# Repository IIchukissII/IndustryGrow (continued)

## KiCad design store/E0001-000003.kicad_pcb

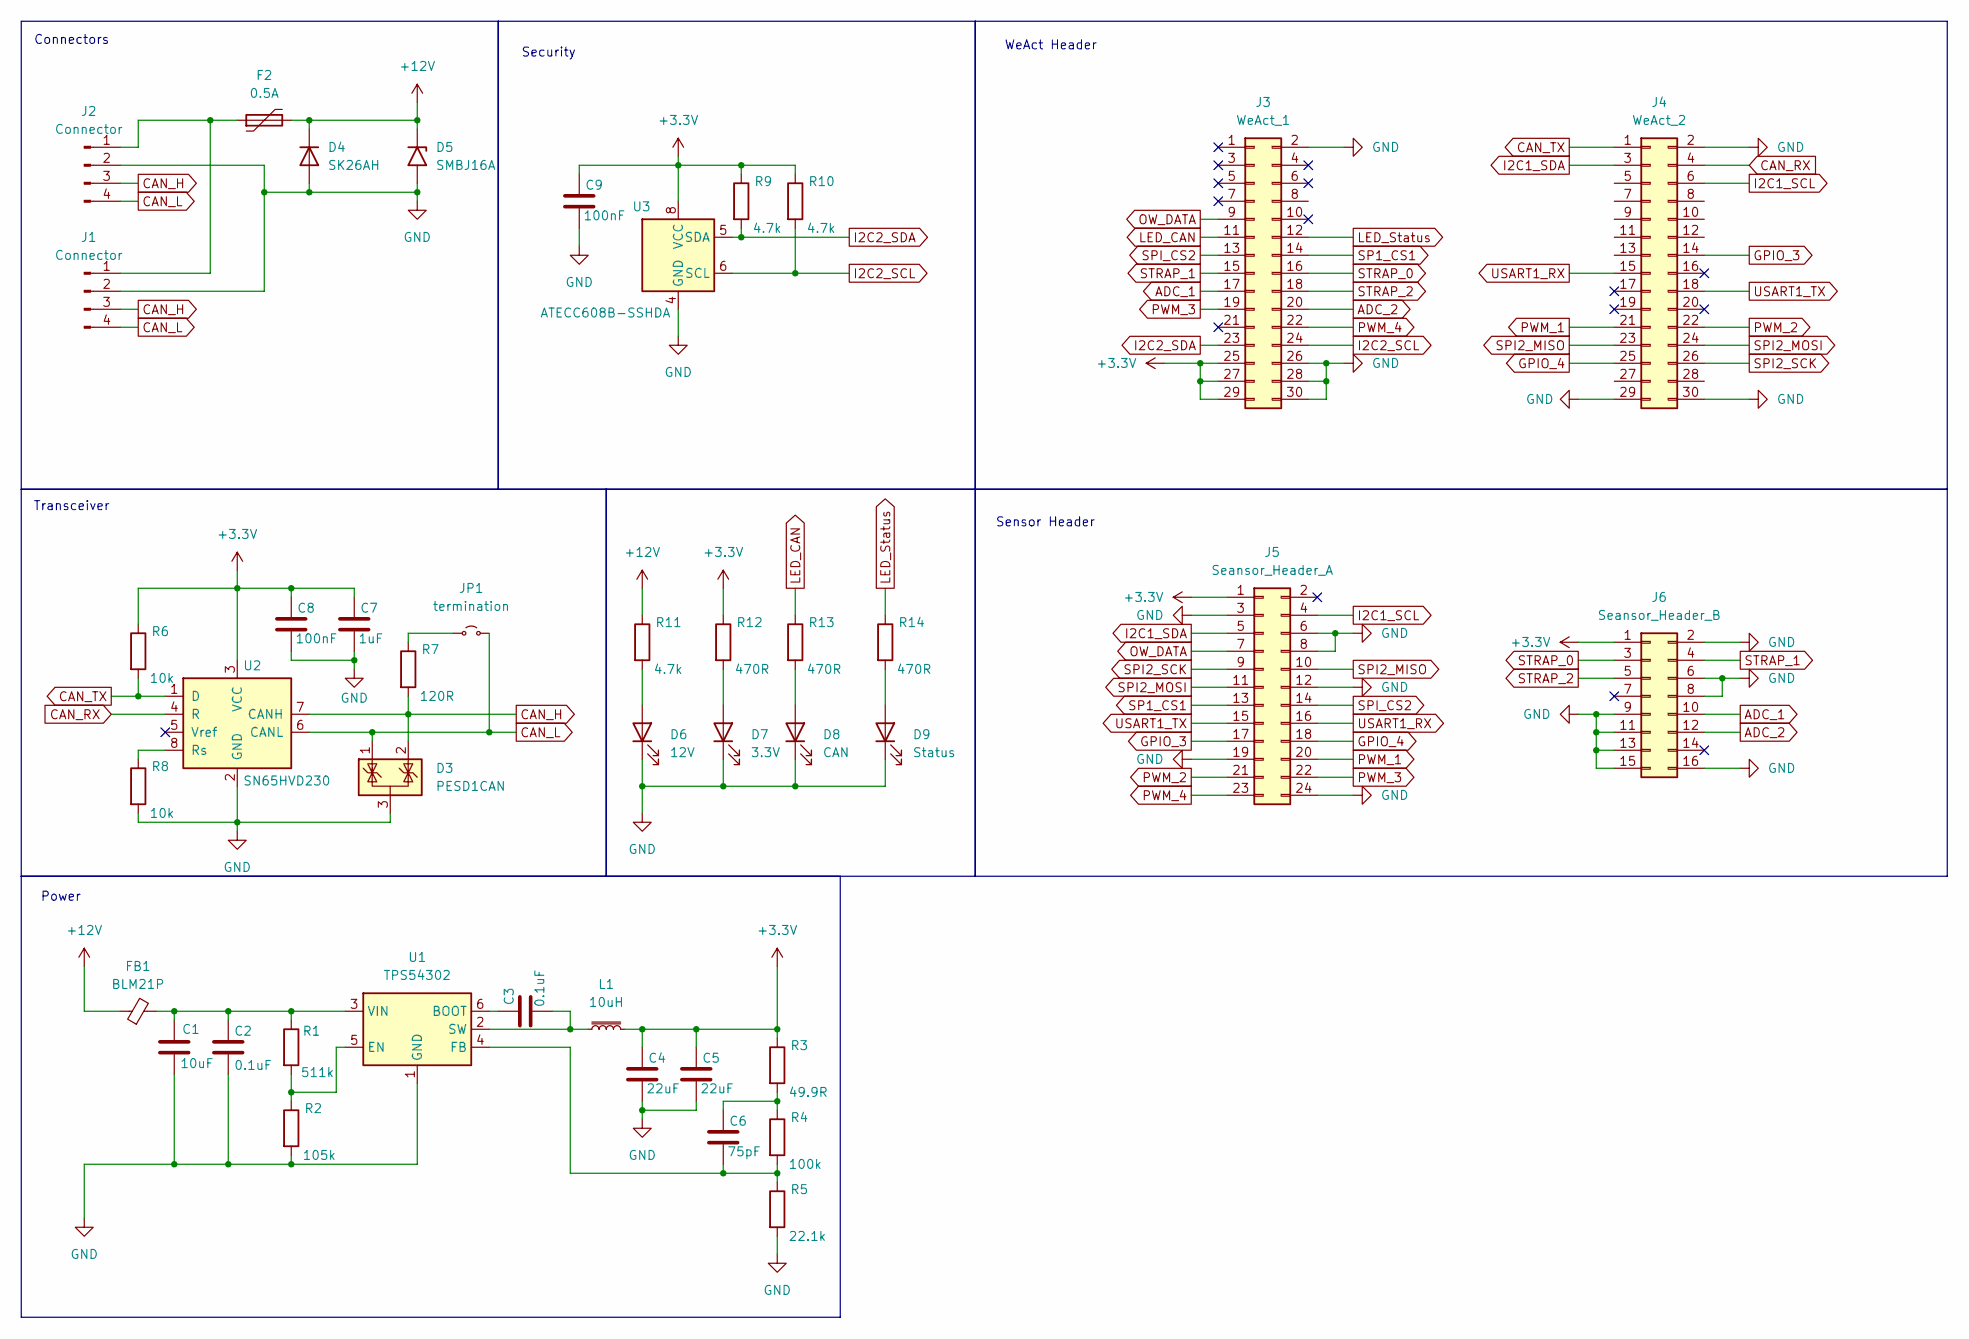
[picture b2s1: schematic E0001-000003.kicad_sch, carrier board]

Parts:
C1: 10uF; C_0805_2012Metric
C2, C3: 0.1uF; C_0805_2012Metric
C4, C5: 22uF; C_0805_2012Metric
C6: 75pF; C_0805_2012Metric
C7: 1uF; C_0805_2012Metric
C8, C9: 100nF; C_0805_2012Metric
D3: PESD1CAN; SOT-23
D4: SK26AH; D_SMA
D5: SMBJ16A; D_SMB
D6: 12V; LED_0805_2012Metric
D7: 3.3V; LED_0805_2012Metric
D8: CAN; LED_0805_2012Metric
D9: Status; LED_0805_2012Metric
F2: 0.5A; Fuse_0805_2012Metric
FB1: BLM21P; Fuse_0805_2012Metric
J1, J2: Connector; Molex_Micro-Fit_3.0_43045-0400_2x02_P3.00mm_Horizontal
J3: WeAct_1; PinSocket_2x15_P2.54mm_Vertical_SMD
J4: WeAct_2; PinSocket_2x15_P2.54mm_Vertical_SMD
J5: Seansor_Header_A; PinSocket_2x12_P2.54mm_Vertical_SMD
J6: Seansor_Header_B; PinSocket_2x08_P2.54mm_Vertical_SMD
JP1: termination; SolderJumper-2_P1.3mm_Open_Pad1.0x1.5mm
L1: 10uH; L_Sunlord_SWPA6045S
R1: 511k; R_0805_2012Metric
R2: 105k; R_0805_2012Metric
R3: 49.9R; R_0805_2012Metric
R4: 100k; R_0805_2012Metric
R5: 22.1k; R_0805_2012Metric
R6, R8: 10k; R_0805_2012Metric
R7: 120R; R_0805_2012Metric
R9, R10, R11: 4.7k; R_0805_2012Metric
R12, R13, R14: 470R; R_0805_2012Metric
U1: TPS54302; SOT-23-6
U2: SN65HVD230; SOIC-8_3.9x4.9mm_P1.27mm
U3: ATECC608B-SSHDA; SOIC-8_3.9x4.9mm_P1.27mm

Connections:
+3.3V: C4.1, C5.1, C7.1, C8.1, C9.1, J3.25, J3.27, J3.29, J5.1, J6.1, L1.2, R3.1, R6.1, R9.1, R10.1, R12.1, U2.3 (VCC), U3.8 (VCC)
+12V: D4.1 (K), D5.1 (A1), F2.2, FB1.1, R11.1
ADC_1: J3.17, J6.10
ADC_2: J3.20, J6.12
CAN_H: D3.2 (K), J1.3, J2.3, R7.2, U2.7 (CANH)
CAN_L: D3.1 (K), J1.4, J2.4, JP1.2 (B), U2.6 (CANL)
CAN_RX: J4.4, U2.4 (R)
CAN_TX: J4.1, R6.2, U2.1 (D)
GND: C1.2, C2.2, C4.2, C5.2, C7.2, C8.2, C9.2, D3.3 (A), D4.2 (A), D5.2 (A2), D6.1 (K), D7.1 (K), D8.1 (K), D9.1 (K), J1.2, J2.2, J3.2, J3.26, J3.28, J3.30, J4.2, J4.29, J4.30, J5.3, J5.6, J5.8, J5.12, J5.19, J5.24, J6.2, J6.6, J6.8, J6.9, J6.11, J6.13, J6.15, J6.16, R2.2, R5.2, R8.2, U1.1 (GND), U2.2 (GND), U3.4 (GND)
GPIO_3: J4.14, J5.17
GPIO_4: J4.25, J5.18
I2C1_SCL: J4.6, J5.4
I2C1_SDA: J4.3, J5.5
I2C2_SCL: J3.24, R10.2, U3.6 (SCL)
I2C2_SDA: J3.23, R9.2, U3.5 (SDA)
LED_CAN: J3.11, R13.1
LED_Status: J3.12, R14.1
unnamed: C6.1, R3.2, R4.1
unnamed: D6.2 (A), R11.2
unnamed: D7.2 (A), R12.2
unnamed: D8.2 (A), R13.2
unnamed: D9.2 (A), R14.2
unnamed: F2.1, J1.1, J2.1
unnamed: JP1.1 (A), R7.1
unnamed: C3.1, U1.6 (BOOT)
unnamed: R1.2, R2.1, U1.5 (EN)
unnamed: C6.2, R4.2, R5.1, U1.4 (FB)
unnamed: C3.2, L1.1, U1.2 (SW)
unnamed: C1.1, C2.1, FB1.2, R1.1, U1.3 (VIN)
unnamed: R8.1, U2.8 (Rs)
OW_DATA: J3.9, J5.7
PWM_1: J4.21, J5.20
PWM_2: J4.22, J5.21
PWM_3: J3.19, J5.22
PWM_4: J3.22, J5.23
SP1_CS1: J3.14, J5.13
SPI2_MISO: J4.23, J5.10
SPI2_MOSI: J4.24, J5.11
SPI2_SCK: J4.26, J5.9
SPI_CS2: J3.13, J5.14
STRAP_0: J3.16, J6.3
STRAP_1: J3.15, J6.4
STRAP_2: J3.18, J6.5
USART1_RX: J4.15, J5.16
USART1_TX: J4.18, J5.15

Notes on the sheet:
Connectors
Power
Sensor Header
Security
WeAct Header
Transceiver

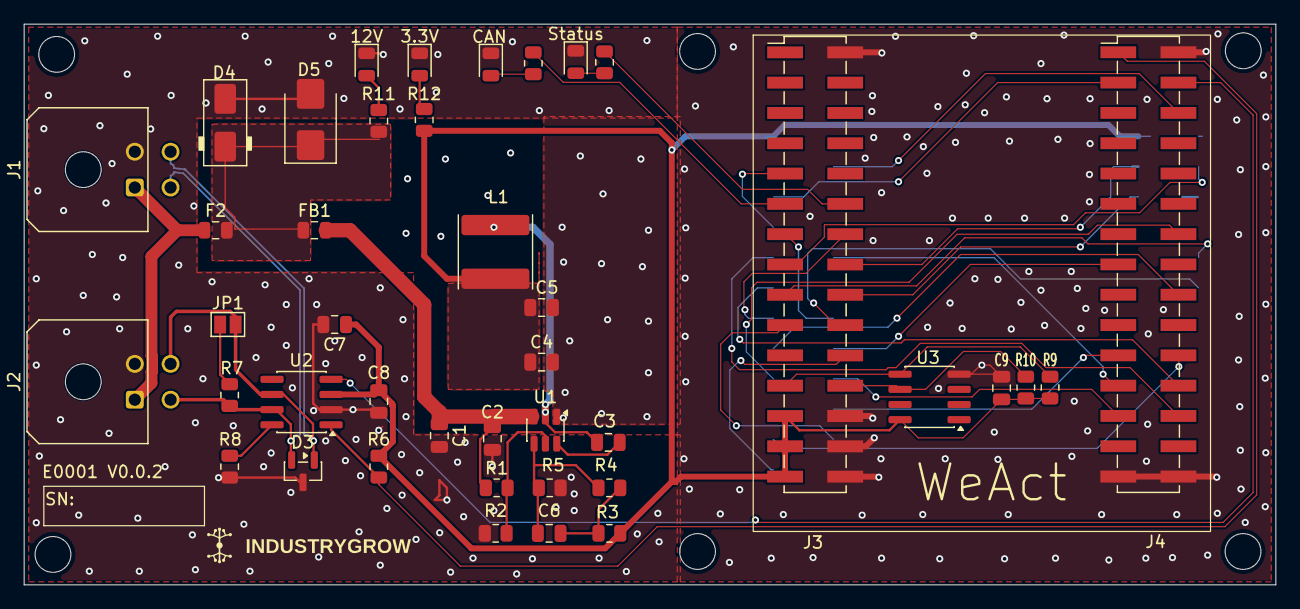
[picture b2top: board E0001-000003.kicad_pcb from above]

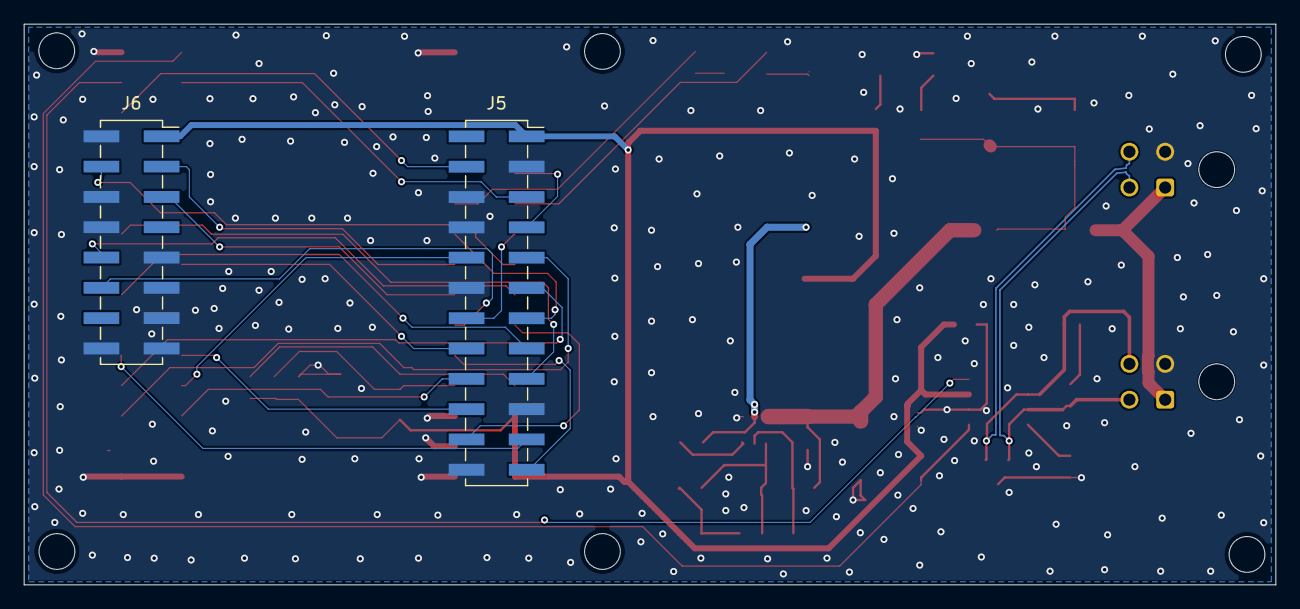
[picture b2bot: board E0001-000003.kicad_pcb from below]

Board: 2 copper layers, 104.9 x 47.0 mm, 44 parts (2 on the bottom side), 45 nets.

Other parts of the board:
IC1: WeAct_1; weact

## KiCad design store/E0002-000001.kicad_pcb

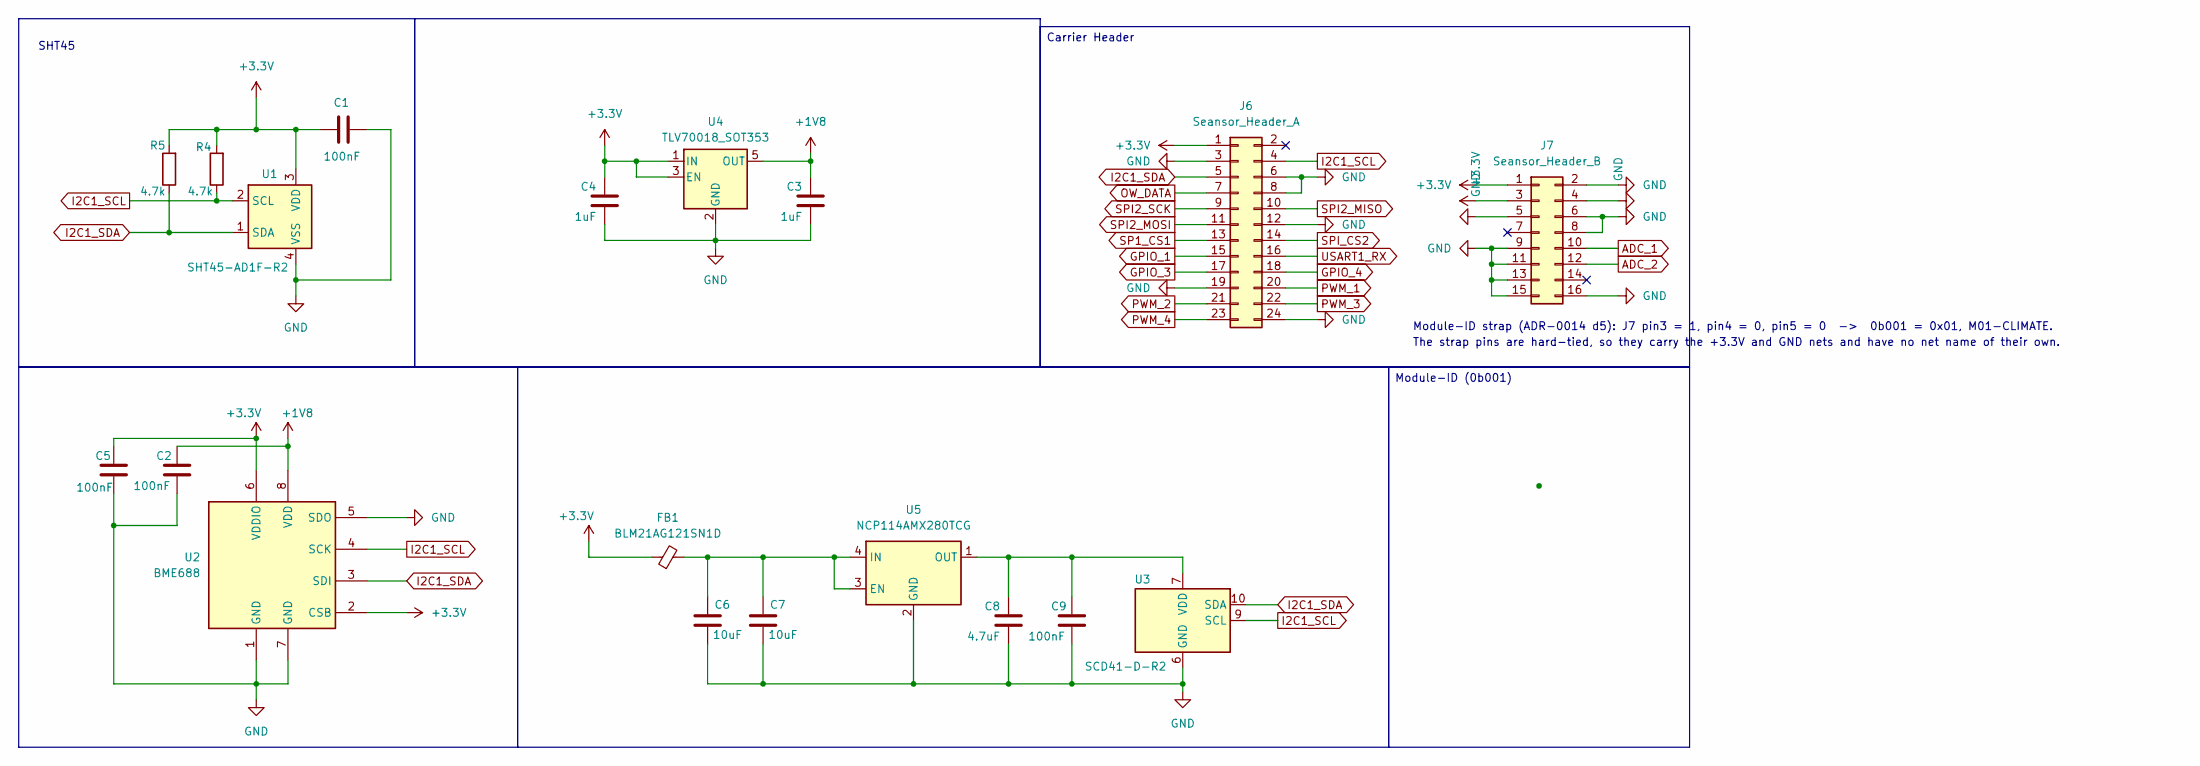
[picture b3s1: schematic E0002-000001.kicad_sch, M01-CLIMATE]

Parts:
C1, C2, C5, C9: 100nF; C_0805_2012Metric
C3, C4: 1uF; C_0805_2012Metric
C6, C7: 10uF; C_0805_2012Metric
C8: 4.7uF; C_0805_2012Metric
FB1: BLM21AG121SN1D; Fuse_0805_2012Metric
J6: Seansor_Header_A; PinHeader_2x12_P2.54mm_Vertical
J7: Seansor_Header_B; PinHeader_2x08_P2.54mm_Vertical
R4, R5: 4.7k; R_0805_2012Metric
U1: SHT45-AD1F-R2; Sensirion_DFN-4_1.5x1.5mm_P0.8mm_SHT4x_NoCentralPad
U2: BME688; Bosch_LGA-8_3x3mm_P0.8mm_ClockwisePinNumbering
U3: SCD41-D-R2; Sensirion_SCD4x-1EP_10.1x10.1mm_P1.25mm_EP4.8x4.8mm
U4: TLV70018_SOT353; SOT-353_SC-70-5
U5: NCP114AMX280TCG; OnSemi_XDFN4-1EP_1.0x1.0mm_EP0.52x0.52mm

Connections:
+1V8: C2.2, C3.2, U2.8 (VDD), U4.5 (OUT)
ADC_1: J7.10
ADC_2: J7.12
GPIO_1: J6.15
GPIO_3: J6.17
GPIO_4: J6.18
I2C1_SCL: J6.4, R4.1, U1.2 (SCL), U2.4 (SCK), U3.9 (SCL)
I2C1_SDA: J6.5, R5.1, U1.1 (SDA), U2.3 (SDI), U3.10 (SDA)
unnamed: C6.1, C7.1, FB1.2, U5.3 (EN), U5.4 (IN)
unnamed: C8.2, C9.2, U3.7 (VDD), U3.19 (VDD), U5.1 (OUT)
OW_DATA: J6.7
PWM_1: J6.20
PWM_2: J6.21
PWM_3: J6.22
PWM_4: J6.23
SP1_CS1: J6.13
SPI2_MISO: J6.10
SPI2_MOSI: J6.11
SPI2_SCK: J6.9
SPI_CS2: J6.14
STRAP_0: C1.1, C4.2, C5.1, FB1.1, J6.1, J7.1, J7.3, R4.2, R5.2, U1.3 (VDD), U2.2 (CSB), U2.6 (VDDIO), U4.1 (IN), U4.3 (EN)
STRAP_1: C1.2, C2.1, C3.1, C4.1, C5.2, C6.2, C7.2, C8.1, C9.1, J6.3, J6.6, J6.8, J6.12, J6.19, J6.24, J7.2, J7.4, J7.5, J7.6, J7.8, J7.9, J7.11, J7.13, J7.15, J7.16, U1.4 (VSS), U2.1 (GND), U2.5 (SDO), U2.7 (GND), U3.6 (GND), U3.20 (GND), U3.21 (GND), U4.2 (GND), U5.2 (GND), U5.5 (GND)
USART1_RX: J6.16

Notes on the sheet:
SHT45
Carrier Header
Module-ID (0b001)
Module-ID strap (ADR-0014 d5): J7 pin3 = 1, pin4 = 0, pin5 = 0 -> 0b001 = 0x01, M01-CLIMATE.
The strap pins are hard-tied, so they carry the +3.3V and GND nets and have no net name of their own.

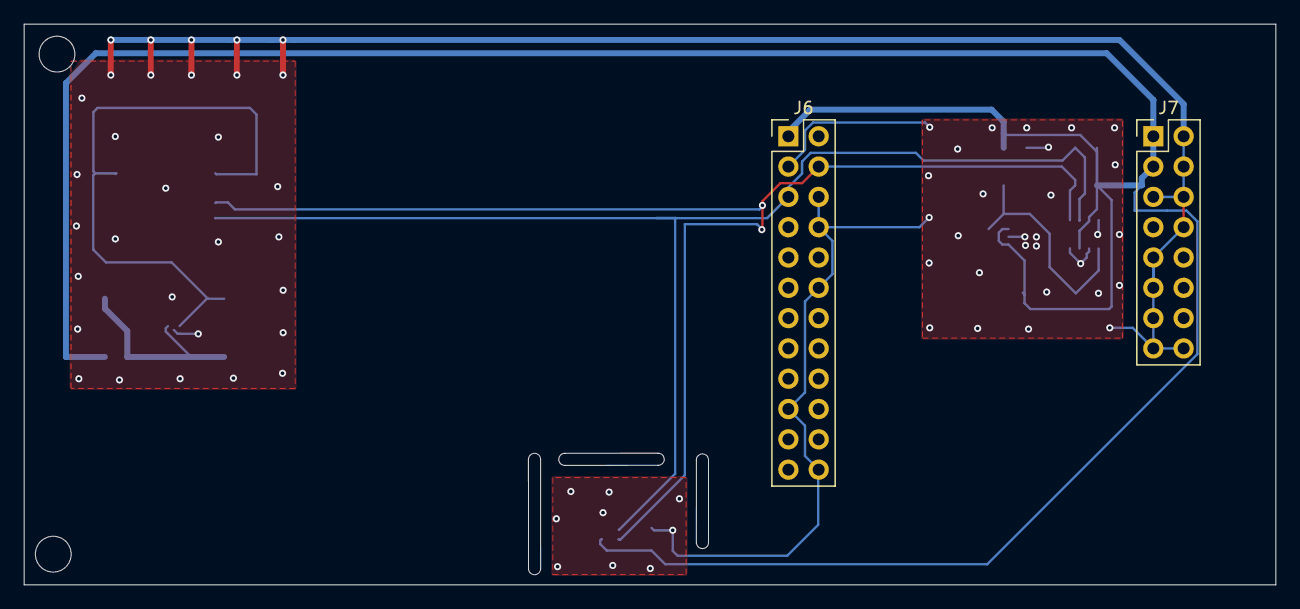
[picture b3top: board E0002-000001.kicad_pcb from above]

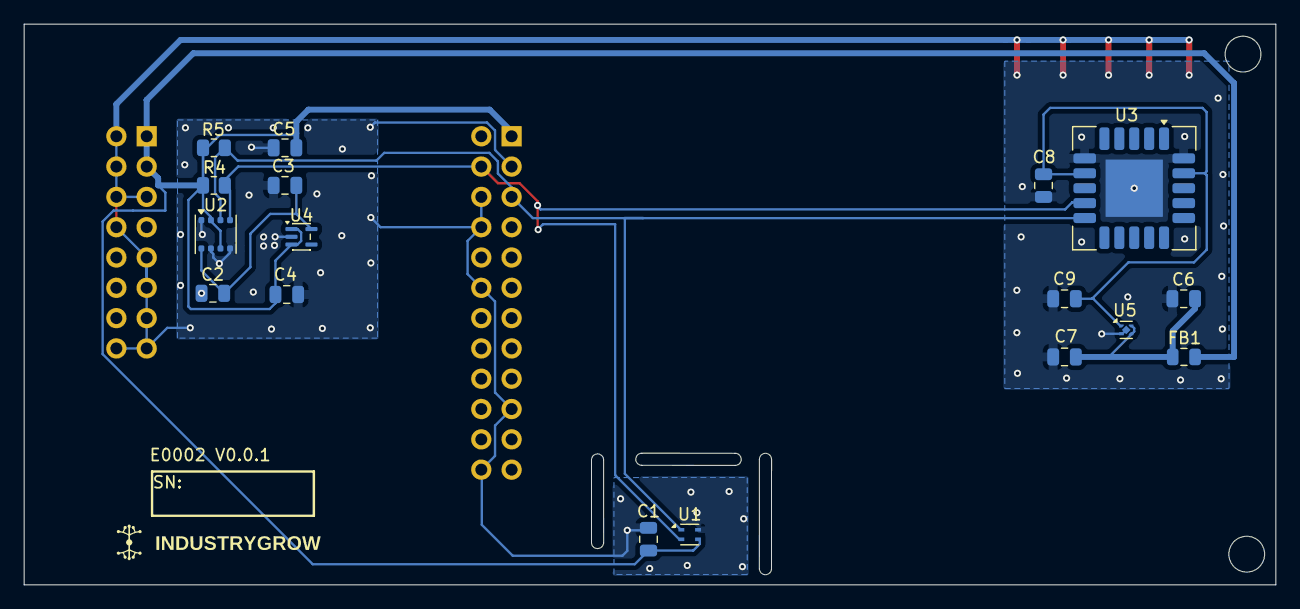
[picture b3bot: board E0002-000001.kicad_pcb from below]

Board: 2 copper layers, 104.9 x 47.0 mm, 19 parts (17 on the bottom side), 7 nets.

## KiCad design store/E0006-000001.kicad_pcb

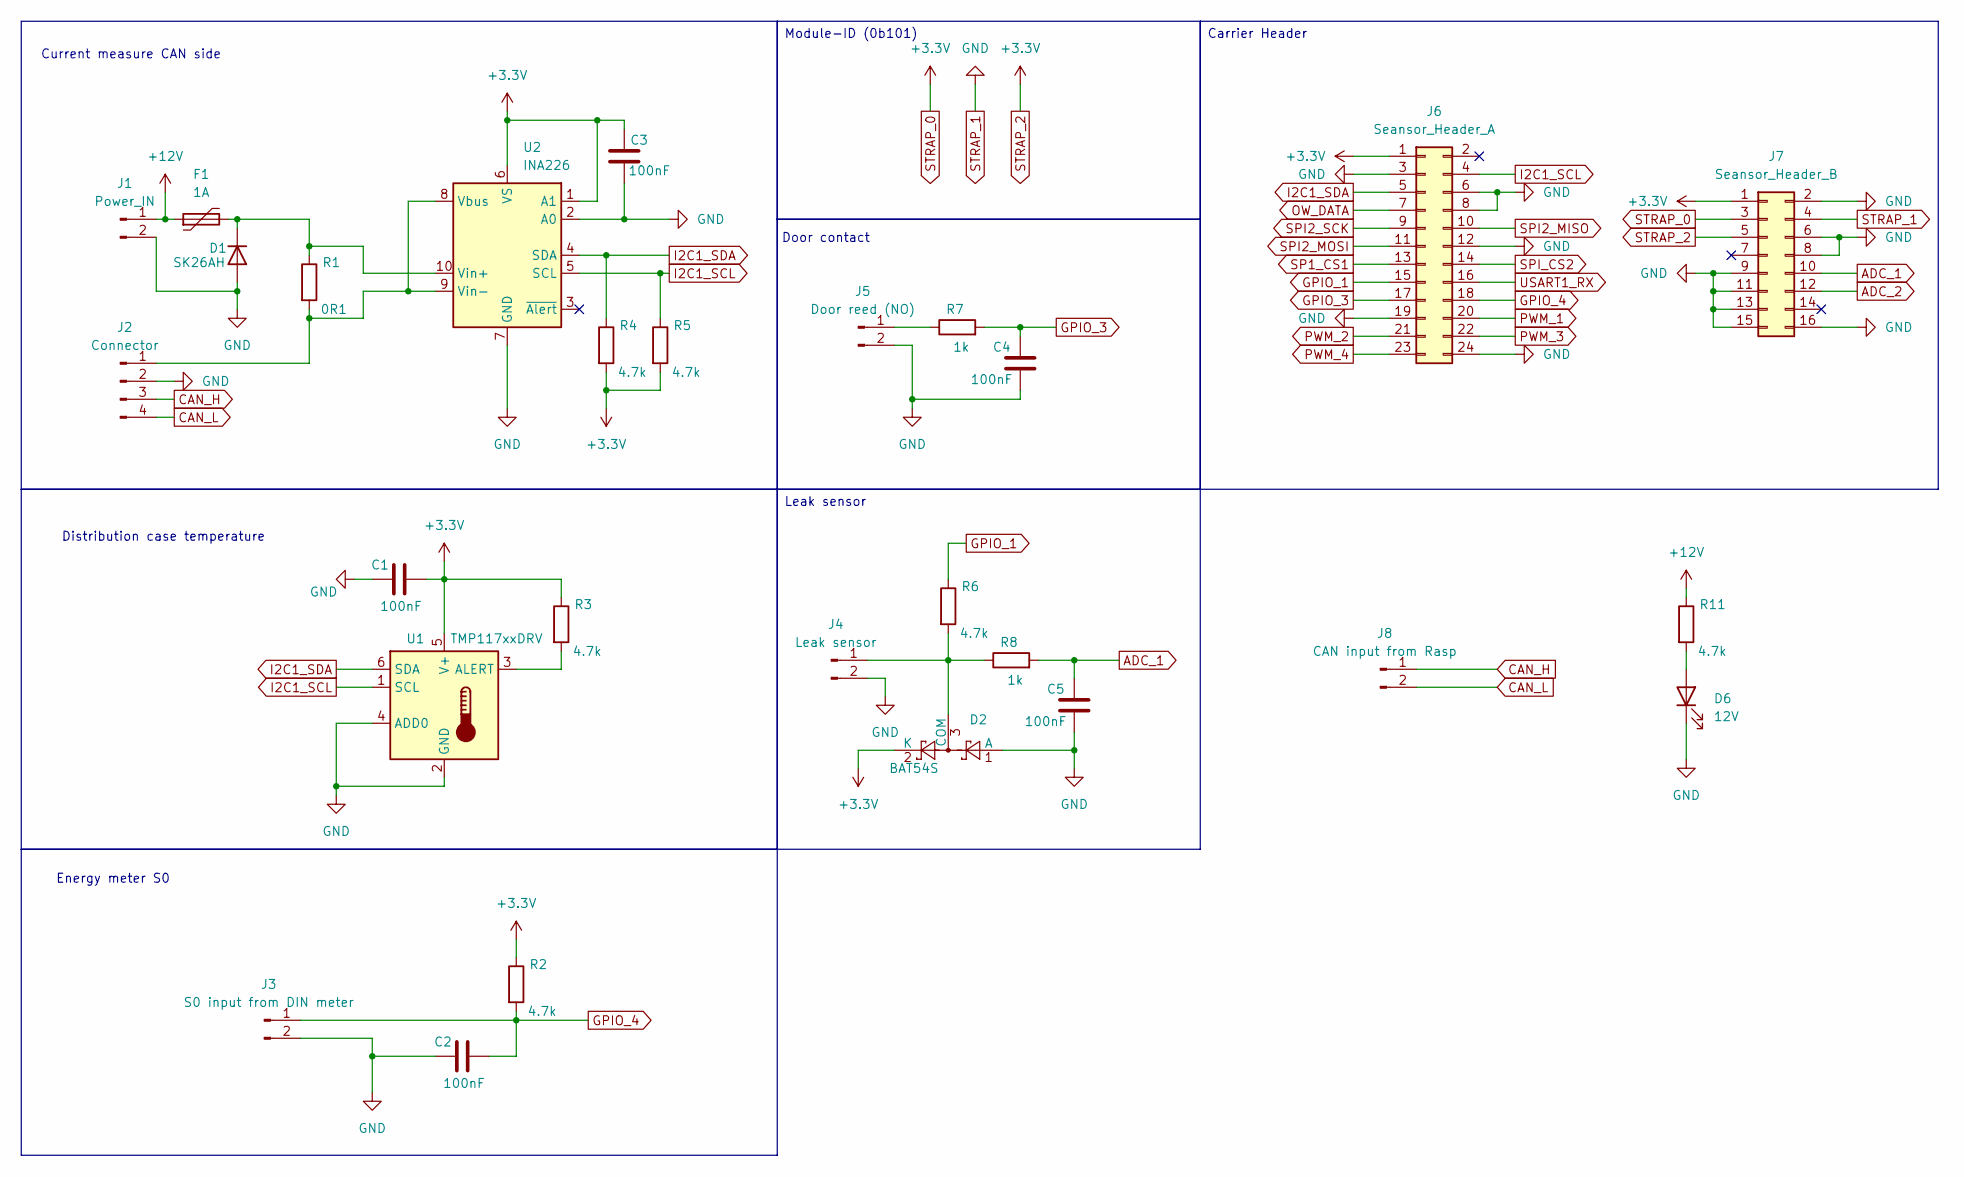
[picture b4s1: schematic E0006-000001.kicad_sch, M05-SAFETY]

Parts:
C1, C2, C3, C4, C5: 100nF; C_0805_2012Metric
D1: SK26AH; D_SMA
D2: BAT54S; SOT-23
D6: 12V; LED_0805_2012Metric
F1: 1A; Fuse_0805_2012Metric
J1: Power_IN; TerminalBlock_Phoenix_MKDS-1,5-2_1x02_P5.00mm_Horizontal
J2: Connector; Molex_Micro-Fit_3.0_43045-0400_2x02_P3.00mm_Horizontal
J3: S0 input from DIN meter; TerminalBlock_Phoenix_MKDS-1,5-2_1x02_P5.00mm_Horizontal
J4: Leak sensor; TerminalBlock_Phoenix_MKDS-1,5-2_1x02_P5.00mm_Horizontal
J5: Door reed (NO); TerminalBlock_Phoenix_MKDS-1,5-2_1x02_P5.00mm_Horizontal
J6: Seansor_Header_A; PinHeader_2x12_P2.54mm_Vertical
J7: Seansor_Header_B; PinHeader_2x08_P2.54mm_Vertical
J8: CAN input from Rasp; TerminalBlock_Phoenix_MKDS-1,5-2_1x02_P5.00mm_Horizontal
R1: 0R1; R_2512_6332Metric
R2, R3, R4, R5, R6, R11: 4.7k; R_0805_2012Metric
R7, R8: 1k; R_0805_2012Metric
U1: TMP117xxDRV; WSON-6-1EP_2x2mm_P0.65mm_EP1x1.6mm
U2: INA226; TSSOP-10_3x3mm_P0.5mm

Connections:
+12V: F1.1, J1.1, R11.1
ADC_1: C5.2, J7.10, R8.2
ADC_2: J7.12
CAN_H: J2.3, J8.1
CAN_L: J2.4, J8.2
GPIO_1: J6.15, R6.1
GPIO_3: C4.2, J6.17, R7.2
GPIO_4: C2.1, J3.1, J6.18, R2.2
I2C1_SCL: J6.4, R5.1, U1.1 (SCL), U2.5 (SCL)
I2C1_SDA: J6.5, R4.1, U1.6 (SDA), U2.4 (SDA)
unnamed: D1.1 (K), F1.2, R1.1, U2.10 (Vin+)
unnamed: D2.3 (COM), J4.1, R6.2, R8.1
unnamed: D6.2 (A), R11.2
unnamed: J2.1, R1.2, U2.8 (Vbus), U2.9 (Vin-)
unnamed: J5.1, R7.1
unnamed: R3.2, U1.3 (ALERT)
OW_DATA: J6.7
PWM_1: J6.20
PWM_2: J6.21
PWM_3: J6.22
PWM_4: J6.23
SP1_CS1: J6.13
SPI2_MISO: J6.10
SPI2_MOSI: J6.11
SPI2_SCK: J6.9
SPI_CS2: J6.14
STRAP_0: C1.1, C3.1, D2.2 (K), J6.1, J7.1, J7.3, J7.5, R2.1, R3.1, R4.2, R5.2, U1.5 (V+), U2.1 (A1), U2.6 (VS)
STRAP_1: C1.2, C2.2, C3.2, C4.1, C5.1, D1.2 (A), D2.1 (A), D6.1 (K), J1.2, J2.2, J3.2, J4.2, J5.2, J6.3, J6.6, J6.8, J6.12, J6.19, J6.24, J7.2, J7.4, J7.6, J7.8, J7.9, J7.11, J7.13, J7.15, J7.16, U1.2 (GND), U1.4 (ADD0), U2.2 (A0), U2.7 (GND)
USART1_RX: J6.16

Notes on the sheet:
Door contact
Energy meter S0
Current measure CAN side
Distribution case temperature
Module-ID (0b101)
Carrier Header
Leak sensor

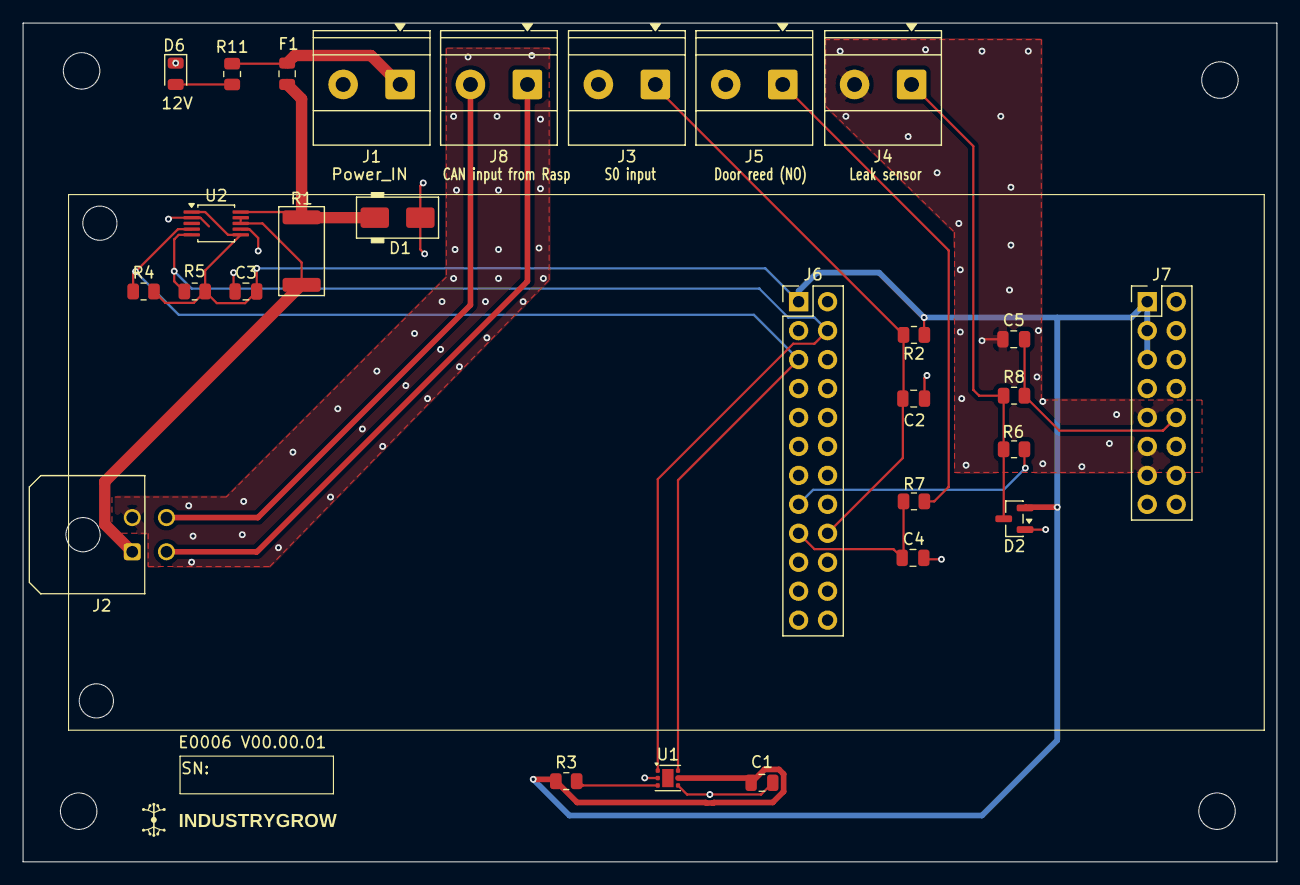
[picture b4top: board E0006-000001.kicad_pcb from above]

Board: 2 copper layers, 110.0 x 73.6 mm, 28 parts (0 on the bottom side), 17 nets.

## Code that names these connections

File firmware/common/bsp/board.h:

/*
 * SPDX-FileCopyrightText: 2026 The IndustryGrow contributors
 * SPDX-License-Identifier: AGPL-3.0-or-later
 */

/*
 * Board support for the IndustryGrow universal carrier (E0001) hosting the
 * WeAct STM32F4 64-Pin Core Board (STM32F405RGT6), populated as the M05-SAFETY
 * node (E0006).
 *
 * Pin assignments below are NOT decided here — the authoritative source is
 * store/E0001-000001-D-pinmap.md. This header only restates them in code form.
 */
#ifndef IGROW_BSP_BOARD_H
#define IGROW_BSP_BOARD_H

#include "stm32f4xx.h" /* CMSIS device header (third_party/cmsis_device_f4) */
#include <stdbool.h>
#include <stdint.h>

/* --- CAN1: PB8 = RX, PB9 = TX, AF9 (pin-map: bxCAN1, 500 kbit/s) --- */
#define BRD_CAN_GPIO        GPIOB
#define BRD_CAN_RX_PIN      8u
#define BRD_CAN_TX_PIN      9u
#define BRD_CAN_AF          9u

/* --- Status / CAN-activity LEDs (pin-map: PA1 = status, PA2 = CAN) --- *
 * Carrier LED polarity is not stated in the pin map; assumed active-high.
 * Flip BRD_LED_ACTIVE_HIGH to 0 if the carrier sinks the LED through the pin. */
#define BRD_LED_ACTIVE_HIGH 1
#define BRD_LED_GPIO        GPIOA
#define BRD_LED_STATUS_PIN  1u
#define BRD_LED_CAN_PIN     2u

/* --- Module-ID straps (pin-map: PA5/PA6/PA7 = STRAP_0/1/2; ADR-0014 d6) --- *
 * Read as inputs with pull-down: a module ties its ID bits to 3V3 (=1) and
 * leaves the 0 bits to the pull-down. KNOWN HARDWARE GAP: on E0001-000001,
 * STRAP_1 (PA6) is unrouted to the MCU (pin-map note / tracked carrier fix),
 * so bit 1 always reads the pull-down 0. That happens to match M05 (0b101),
 * but it is a real gap for M02/M03/M06 — see board_read_module_id(). */
#define BRD_STRAP_GPIO      GPIOA
#define BRD_STRAP0_PIN      5u
#define BRD_STRAP1_PIN      6u  /* unrouted on E0001-000001 */
#define BRD_STRAP2_PIN      7u

/* --- Debug UART: USART1 PA9 = TX, PA10 = RX, AF7 (bench bring-up only) --- *
 * These pins are GPIO_1/GPIO_2 on the sensor-module header; M05 uses GPIO_3/4
 * (reed/S0), so PA9/PA10 are free for a debug console on the bench. */
#define BRD_DBG_UART        USART1
#define BRD_DBG_GPIO        GPIOA
#define BRD_DBG_TX_PIN      9u
#define BRD_DBG_RX_PIN      10u
#define BRD_DBG_AF          7u
#define BRD_DBG_BAUD        115200u

/* Module-ID strap pattern expected for M05-SAFETY (ADR-0014 d6: 0b101). */
#define BRD_MODULE_ID_M05   0x5u

/* Bring up GPIO clocks and configure LEDs + straps. Call after clock_init(). */
void board_init(void);

/* Read the 3-bit module-ID strap pattern (bit0=STRAP_0 .. bit2=STRAP_2).
 * Bit 1 is forced to 0 on E0001-000001 (STRAP_1/PA6 unrouted, see above). */
uint8_t board_read_module_id(void);

void board_led_status(bool on);
void board_led_can(bool on);
void board_led_status_toggle(void);

#endif /* IGROW_BSP_BOARD_H */
